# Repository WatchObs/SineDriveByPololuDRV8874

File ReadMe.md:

Stepper motor driver using two DRV8874 Pololu assemblies for direct and FOC control, AS5047D magnetic position sensing assembly and RS485 assembly. Teensy 4.0 via Arduino IDE to code control of these assemblies. 
The emphasis is control of a Right Ascension axis of an equatorial telescope as the original Makerbase Servo57D did not allow for reducing a rythmic 1+ arcsec variation due to motor pole differences as Makerbase does not provide open sources or access to the processor. In sidereal and pulse tracking mode, direct current control (D axis in D-Q rotor frame of reference) is used as FOC at the 0.25 RPM does not allow sufficient finesse (the stepper is driving a worm directly that drives a 360 tooth gear, 0.25 RPM equates to sidereal), and FOC for slewing.

The board mounted on the back of a Nema 23 stepper for the AS5047D, or if an external (glass type) ABI encoder is used, jumpers provide that programmation.

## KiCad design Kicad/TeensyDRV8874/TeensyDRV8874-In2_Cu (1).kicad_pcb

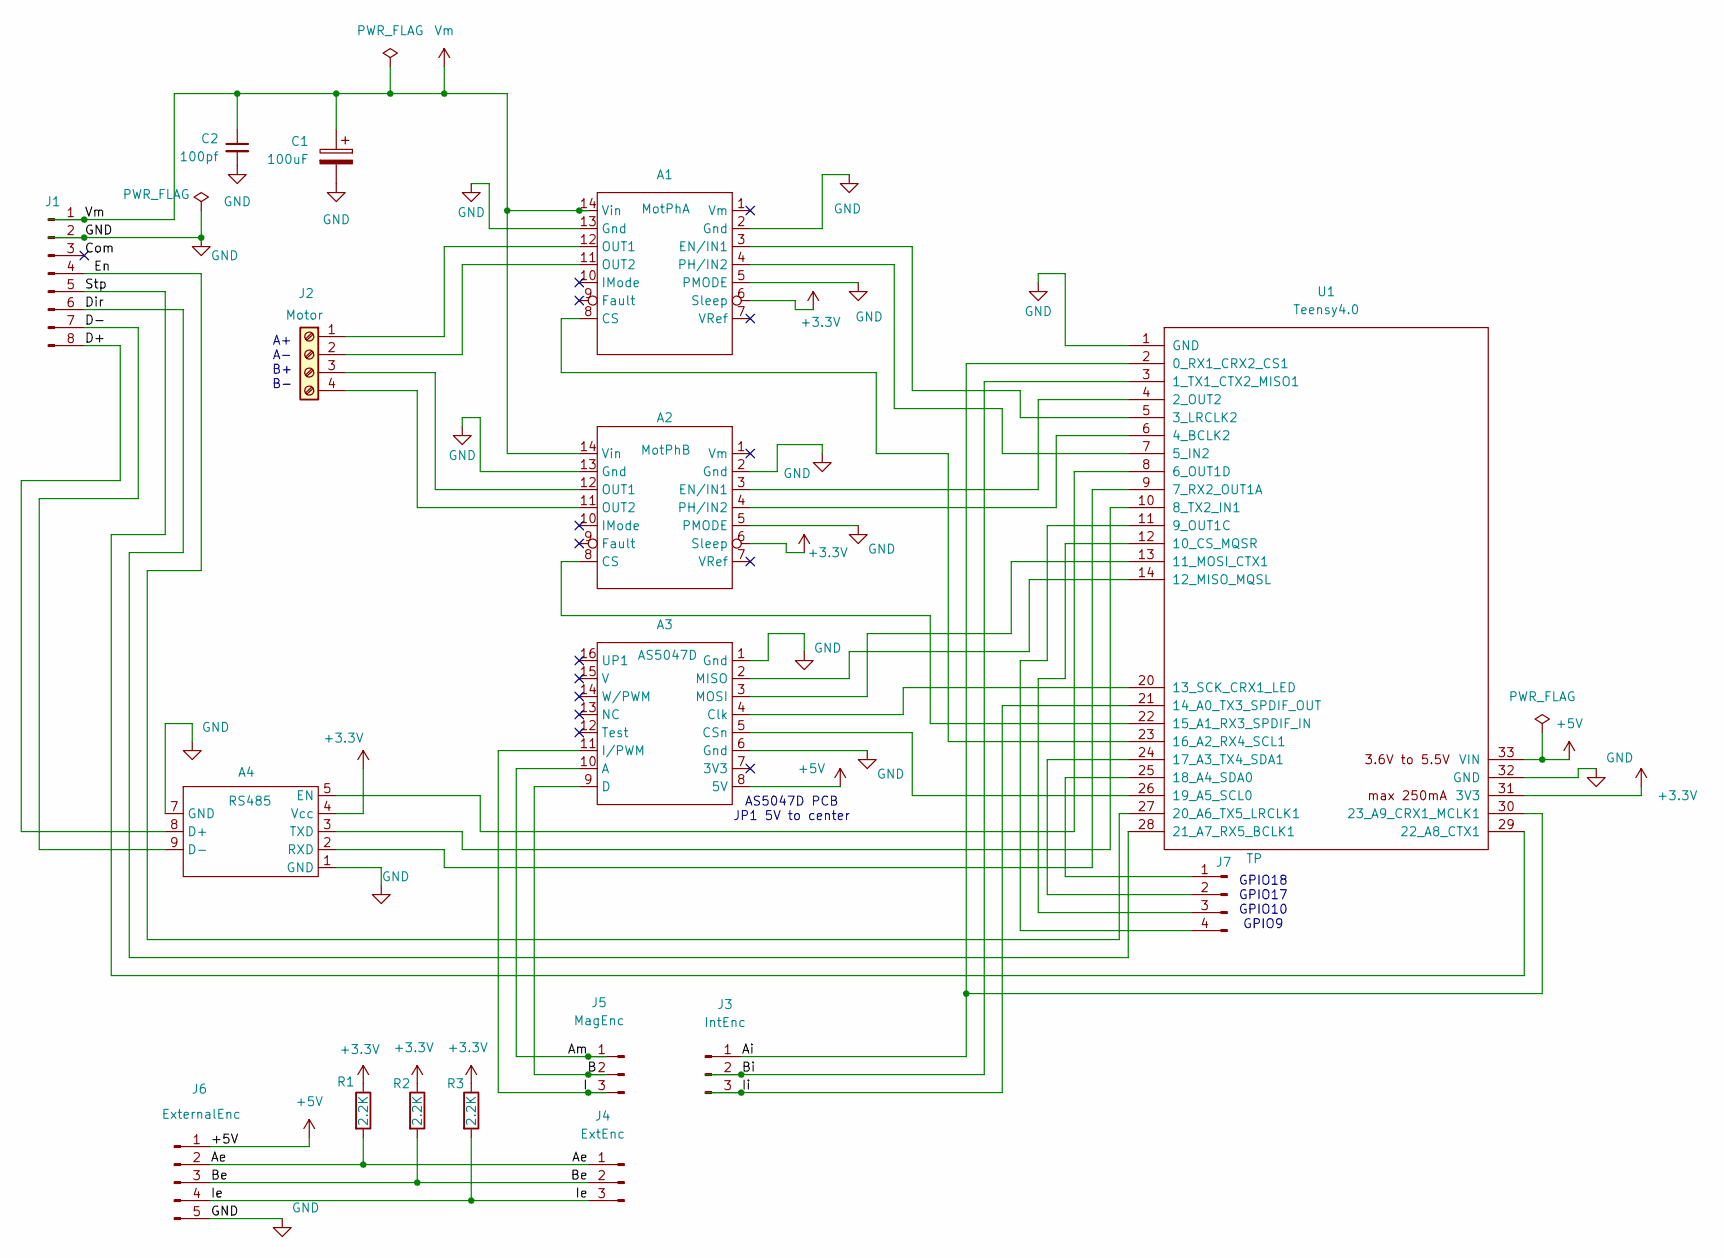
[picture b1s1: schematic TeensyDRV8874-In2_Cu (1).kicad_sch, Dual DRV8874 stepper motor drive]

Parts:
A1: MotPhA; DRV8874
A2: MotPhB; DRV8874
A3: AS5047D
A4: RS485
C1: 100uF; CP_Radial_D8.0mm_P2.50mm
C2: 100pf; C_Disc_D5.0mm_W2.5mm_P5.00mm
J1: PinHeader_1x08_P2.54mm_Vertical
J2: Motor; TerminalBlock-1x04_P2.54mm_Horizontal
J3: IntEnc; PinHeader_1x03_P2.54mm_Vertical
J4: ExtEnc; PinHeader_1x03_P2.54mm_Vertical
J5: MagEnc; PinHeader_1x03_P2.54mm_Vertical
J6: ExternalEnc; PinHeader_1x05_P2.54mm_Vertical
J7: TP; PinHeader_1x04_P2.54mm_Vertical
R1, R2, R3: 2.2K; R_Axial_DIN0204_L3.6mm_D1.6mm_P2.54mm_Vertical
U1: Teensy4.0; Teensy40

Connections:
+3.3V: A1.6 (Sleep), A2.6 (Sleep), A4.4 (Vcc), R1.1, R2.1, R3.1, U1.31 (3V3)
+5V: A3.8 (5V), J6.1 (+5V), U1.33 (VIN)
/Ae: J4.1 (Ae), J6.2 (Ae), R1.2
/Ai: J3.1 (Ai), U1.2 (0_RX1_CRX2_CS1), U1.30 (23_A9_CRX1_MCLK1)
/Am: A3.10 (A), J5.1 (Am)
/B: A3.9 (D), J5.2 (Bm)
/Be: J4.2 (Be), J6.3 (Be), R2.2
/Bi: J3.2 (Bi), U1.3 (1_TX1_CTX2_MISO1)
/Com: J1.3 (Com)
/D+: A4.8 (D+), J1.8 (D+)
/D-: A4.9 (D-), J1.7 (D-)
/Dir: J1.6 (Dir), U1.28 (21_A7_RX5_BCLK1)
/En: J1.4 (En), U1.27 (20_A6_TX5_LRCLK1)
/I: A3.11 (I/PWM), J5.3 (Im)
/Ie: J4.3 (Ie), J6.4 (Ie), R3.2
/Ii: J3.3 (Ii), U1.21 (14_A0_TX3_SPDIF_OUT)
/Stp: J1.5 (Stp), U1.29 (22_A8_CTX1)
GND: A1.2 (Gnd), A1.5 (PMODE), A1.13 (Gnd), A2.2 (Gnd), A2.5 (PMODE), A2.13 (Gnd), A3.1 (Gnd), A3.6 (Gnd), A4.1 (GND), A4.7 (GND), C1.2, C2.2, J1.2 (GND), J6.5 (GND), U1.1 (GND), U1.32 (GND)
unnamed: A1.8 (CS), U1.23 (16_A2_RX4_SCL1)
unnamed: A1.3 (EN/IN1), U1.5 (3_LRCLK2)
unnamed: A1.12 (OUT1), J2.1 (A+)
unnamed: A1.11 (OUT2), J2.2 (A-)
unnamed: A1.4 (PH/IN2), U1.7 (5_IN2)
unnamed: A2.8 (CS), U1.22 (15_A1_RX3_SPDIF_IN)
unnamed: A2.3 (EN/IN1), U1.4 (2_OUT2)
unnamed: A2.12 (OUT1), J2.3 (B+)
unnamed: A2.11 (OUT2), J2.4 (B-)
unnamed: A2.4 (PH/IN2), U1.6 (4_BCLK2)
unnamed: A3.5 (CSn), U1.26 (19_A5_SCL0)
unnamed: A3.4 (Clk), U1.20 (13_SCK_CRX1_LED)
unnamed: A3.2 (MISO), U1.14 (12_MISO_MQSL)
unnamed: A3.3 (MOSI), U1.13 (11_MOSI_CTX1)
unnamed: A4.5 (EN), U1.8 (6_OUT1D)
unnamed: A4.2 (RXD), U1.9 (7_RX2_OUT1A)
unnamed: A4.3 (TXD), U1.10 (8_TX2_IN1)
unnamed: J7.1, U1.25 (18_A4_SDA0)
unnamed: J7.2, U1.24 (17_A3_TX4_SDA1)
unnamed: J7.3, U1.12 (10_CS_MQSR)
unnamed: J7.4, U1.11 (9_OUT1C)
Vm: A1.14 (Vin), A2.14 (Vin), C1.1, C2.1, J1.1 (+15V)

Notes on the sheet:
GPIO18 GPIO17 GPIO10 GPIO9
AS5047D PCB JP1 5V to center
A+ A- B+ B-

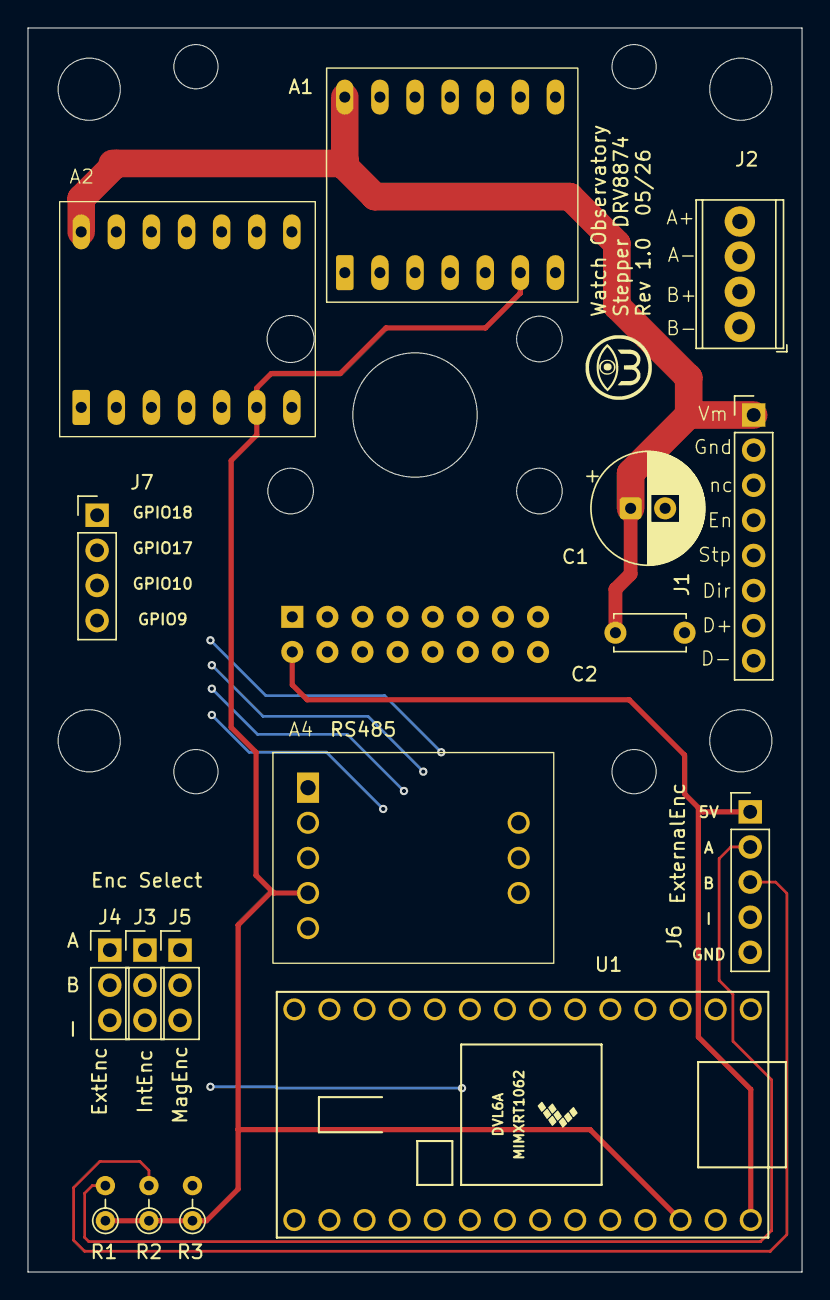
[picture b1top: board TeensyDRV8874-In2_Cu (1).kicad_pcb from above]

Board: 4 copper layers, 56.0 x 90.0 mm, 18 parts (1 on the bottom side), 39 nets.

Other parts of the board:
Nema23: MountingHole_4.5mm

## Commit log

2026-02-08 Numerous testing improvements
2026-03-04 Name change, multiple improvements
    File name change, D-Q currents, PI servo, glass disk encoder input (2500ppr), etc
2026-03-08 work in progress
    Work in progress.... FOC d-q velocity computation...
2026-03-16 implemented FOC further
    - no longer using sine LUT, using sin/cos math
    - no longer using 8 step
    - using direct mode at low RPM with position servo only
    - using FOC for high speeds with velocity servo only
    - using period counter for encoder > motor speed
2026-03-18 Update SineDriveByPololuDRV8874.ino
    Working with AI - made accessible for work with
2026-03-22 Update SineDriveByPololuDRV8874.ino
    FOC <> direct transition. Need further work on direct >> FOC, and solution isn't best of class...
2026-03-27 Update SineDriveByPololuDRV8874.ino
    Working glitches from transitions across 0<>360 boundaries
2026-03-29 Update SineDriveByPololuDRV8874.ino
    At sideral rates ( near 0.25 RPM), reduced per ISR iteration slew to prevent glitches from occasional incorrect freq signal
2026-03-29 Update SineDriveByPololuDRV8874.ino
    Corrected diff limit on low RPM
2026-05-12 Nema23 back end card mount,
    Supports back end magnet or quad encoder
2026-05-12 root markdown added
2026-05-12 Add image to ReadMe file
2026-05-12 Enhance ReadMe with project details and control methods
    Added detailed project description and usage information.
2026-05-12 Enhance ReadMe with board mounting details
    Added additional information about board mounting options for encoders.
2026-06-07 Update after fully functional PCB and motor + software
2026-06-07 Update ReadMe with additional image and content
    Added an image link for the DRV8874 stepper motor driver.
2026-06-07 Folder Clean up
2026-06-19 OpenScad housing for RPi Zero 2W and laser
2026-06-19 File in wrong repo - removing
2026-06-20 Worked external encoder version
    ..and made code more easily switching between AS5074D and external encoder. Added standalone housing for when external encoder is used
2026-06-22 Further working direct mode servo
